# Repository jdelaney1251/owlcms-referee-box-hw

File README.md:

# OWLCMS Wireless Referee Decision Box

This is an open source hardware design for the OWLCMS Wireless Referee decision 
box firmware which can be found at [owlcms-referee-box-fw](https://github.com/jdelaney1251/owlcms-referee-box-fw)

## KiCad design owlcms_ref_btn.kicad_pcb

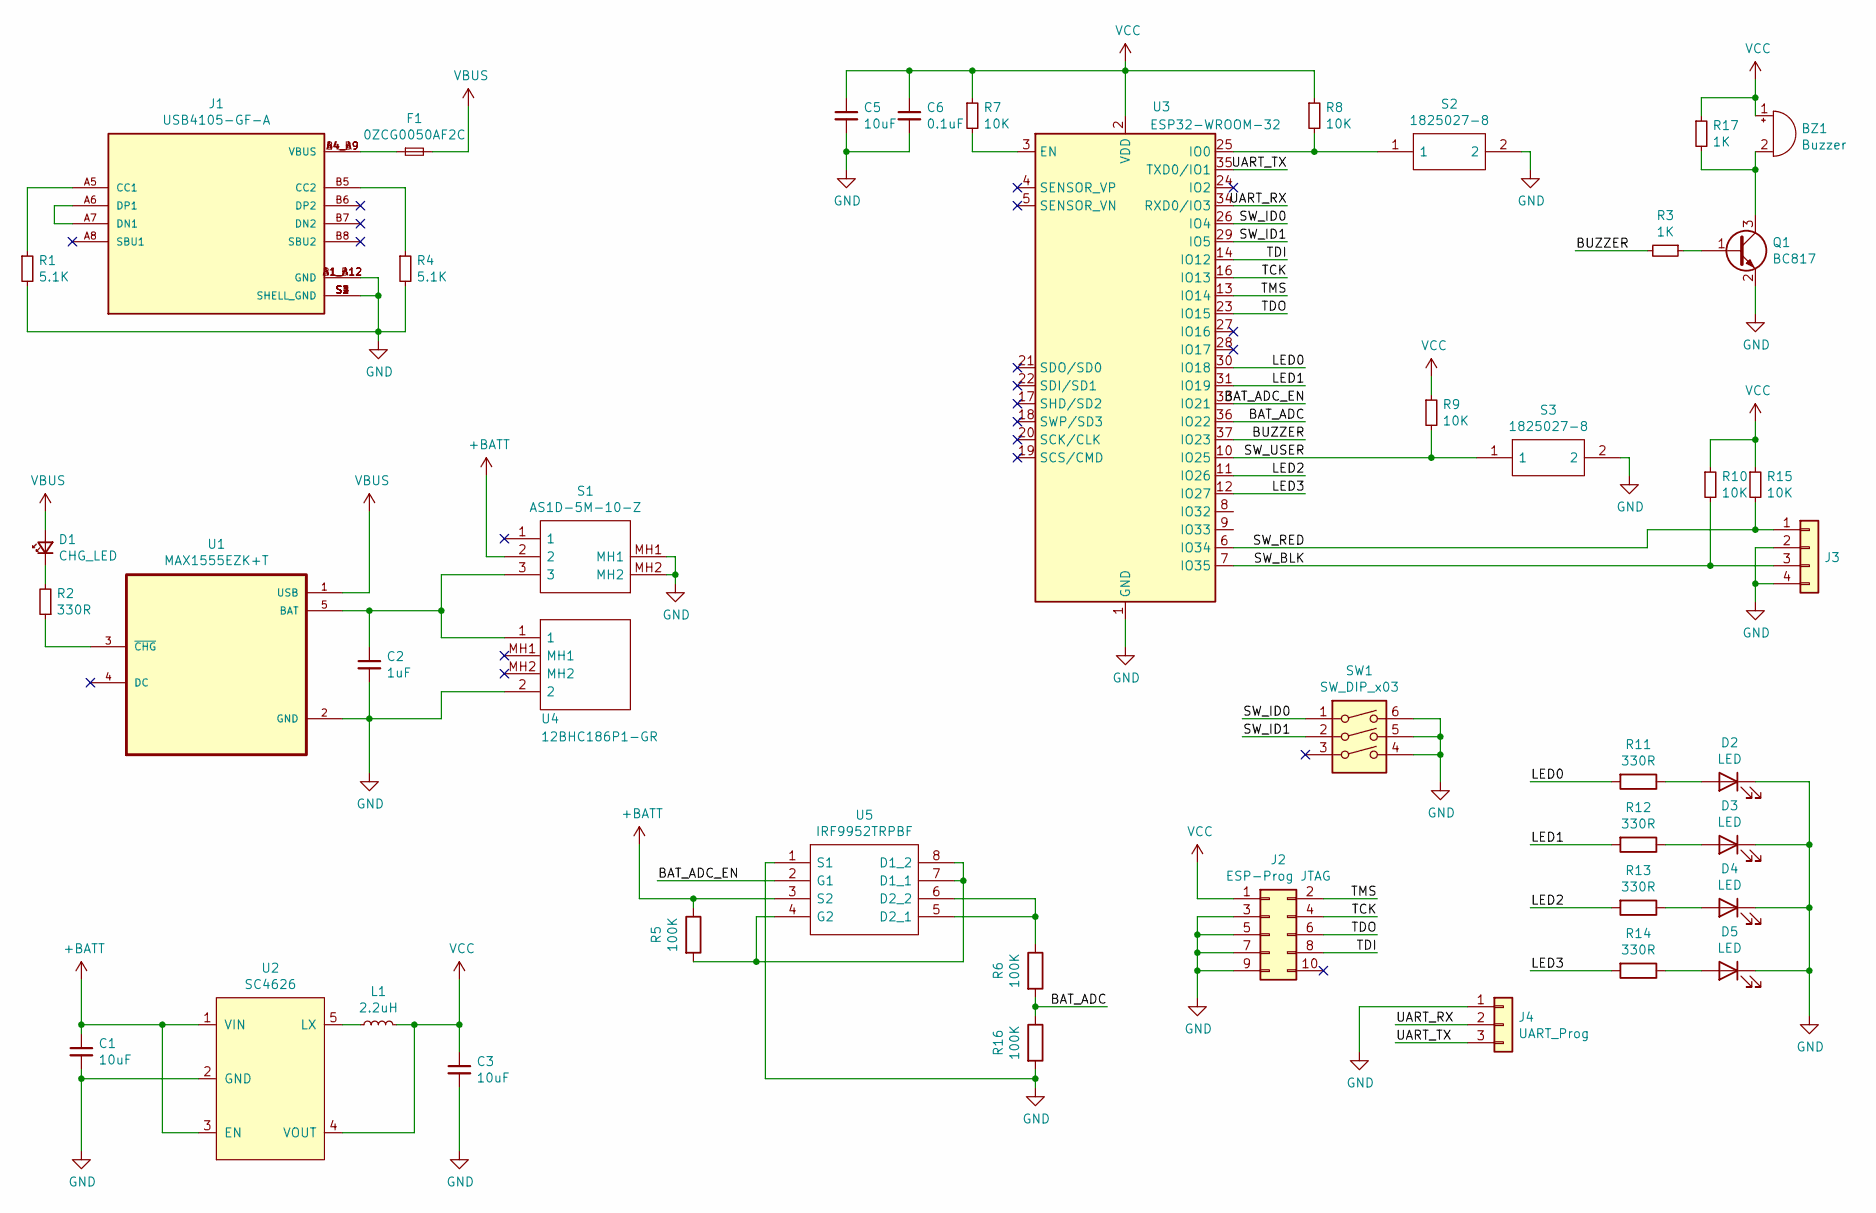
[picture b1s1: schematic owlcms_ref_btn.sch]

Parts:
BZ1: Buzzer; Buzzer_12x9.5RM6.5
C1, C3, C5: 10uF; C_0805_2012Metric_Pad1.18x1.45mm_HandSolder
C2: 1uF; C_0805_2012Metric_Pad1.18x1.45mm_HandSolder
C6: 0.1uF; C_0805_2012Metric_Pad1.18x1.45mm_HandSolder
D1: CHG_LED; APA2107LSYCKJ3PRV
D2, D3, D4, D5: LED; APA2107LSYCKJ3PRV
F1: 0ZCG0050AF2C; Fuse_1812_4532Metric
J1: USB4105-GF-A; GCT_USB4105-GF-A; PARTREV A3
J2: ESP-Prog JTAG; PinHeader_2x05_P1.27mm_Vertical
J3: Conn_01x04; PinHeader_1x04_P2.54mm_Vertical
J4: UART_Prog; PinHeader_1x03_P2.54mm_Vertical
L1: 2.2uH; L_0805_2012Metric
Q1: BC817; SOT-23
R1, R4: 5.1K; R_0805_2012Metric
R2, R11, R12, R13, R14: 330R; R_0805_2012Metric
R3, R17: 1K; R_0805_2012Metric
R5, R6, R16: 100K; R_0805_2012Metric
R7, R8, R9, R10, R15: 10K; R_0805_2012Metric
S1: AS1D-5M-10-Z; AS1D5M10Z; Manufacturer_Part_Number AS1D-5M-10-Z
S2, S3: 1825027-8; Mouser Part Number 506-1825027-8
SW1: SW_DIP_x03; SW_DIP_SPSTx03_Slide_6.7x9.18mm_W7.62mm_P2.54mm_LowProfile
U1: MAX1555EZK+T; SOT-23-5_HandSoldering
U2: SC4626; SOT-23-5
U3: ESP32-WROOM-32
U4: 12BHC186P1-GR; 12BHC186P1GR; Mouser Part Number 12BHC186P1-GR
U5: IRF9952TRPBF; SOIC127P600X175-8N; Mouser Part Number 942-IRF9952TRPBF

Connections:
+BATT: C1.1, R5.1, S1.2, U2.1 (VIN), U2.3 (EN), U5.3 (S2)
/BAT_ADC: R6.2, R16.1, U3.36 (IO22)
/BAT_ADC_EN: U3.33 (IO21), U5.2 (G1)
/BUZZER: R3.2, U3.37 (IO23)
/LED0: R11.2, U3.30 (IO18)
/LED1: R12.2, U3.31 (IO19)
/LED2: R13.2, U3.11 (IO26)
/LED3: R14.2, U3.12 (IO27)
/SW_BLK: J3.3, R10.2, U3.7 (IO35)
/SW_ID0: SW1.1, U3.26 (IO4)
/SW_ID1: SW1.2, U3.29 (IO5)
/SW_RED: J3.1, R15.2, U3.6 (IO34)
/SW_USER: R9.2, S3.1, U3.10 (IO25)
/TCK: J2.4, U3.16 (IO13)
/TDI: J2.8, U3.14 (IO12)
/TDO: J2.6, U3.23 (IO15)
/TMS: J2.2, U3.13 (IO14)
/UART_RX: J4.2, U3.34 (RXD0/IO3)
/UART_TX: J4.3, U3.35 (TXD0/IO1)
GND: C1.2, C2.2, C3.2, C5.2, C6.2, D2.1 (K), D3.1 (K), D4.1 (K), D5.1 (K), J1.A1_B12 (GND), J1.B1_A12 (GND), J1.S1 (SHELL_GND), J1.S2 (SHELL_GND), J1.S3 (SHELL_GND), J1.S4 (SHELL_GND), J2.3, J2.5, J2.7, J2.9, J3.2, J3.4, J4.1, Q1.2 (E), R1.2, R4.2, R16.2, S1.MH1, S1.MH2, S2.2, S3.2, SW1.4, SW1.5, SW1.6, U1.2 (GND), U2.2 (GND), U3.1 (GND), U3.15 (GND), U3.38 (GND), U3.39 (GND), U4.2, U5.1 (S1)
unnamed: BZ1.2 (+), Q1.3 (C), R17.2
unnamed: C2.1, S1.3, U1.5 (BAT), U4.1
unnamed: D1.1 (K), R2.2
unnamed: D2.2 (A), R11.1
unnamed: D3.2 (A), R12.1
unnamed: D4.2 (A), R13.1
unnamed: D5.2 (A), R14.1
unnamed: F1.1, J1.A4_B9 (VBUS), J1.B4_A9 (VBUS)
unnamed: J1.A5 (CC1), R1.1
unnamed: J1.A6 (DP1), J1.A7 (DN1)
unnamed: J1.B5 (CC2), R4.1
unnamed: L1.1, U2.5 (LX)
unnamed: Q1.1 (B), R3.1
unnamed: R2.1, U1.3 (~CHG)
unnamed: R5.2, U5.4 (G2), U5.7 (D1_1), U5.8 (D1_2)
unnamed: R6.1, U5.5 (D2_1), U5.6 (D2_2)
unnamed: R7.2, U3.3 (EN)
unnamed: R8.2, S2.1, U3.25 (IO0)
VBUS: D1.2 (A), F1.2, U1.1 (USB)
VCC: BZ1.1 (-), C3.1, C5.1, C6.1, J2.1, L1.2, R7.1, R8.1, R9.1, R10.1, R15.1, R17.1, U2.4 (VOUT), U3.2 (VDD)

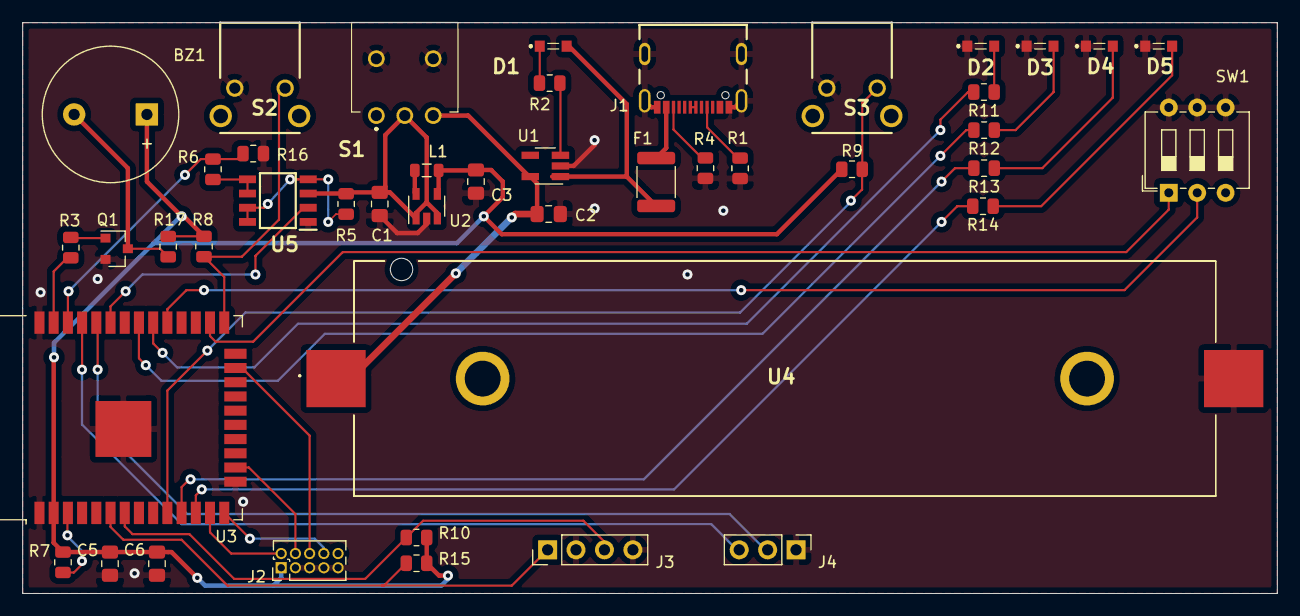
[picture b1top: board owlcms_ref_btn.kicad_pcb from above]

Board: 4 copper layers, 112.1 x 51.0 mm, 44 parts (0 on the bottom side), 40 nets.

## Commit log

2022-09-11 initial rev1 commit
